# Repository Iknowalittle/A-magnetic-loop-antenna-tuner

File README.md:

This is a simple proto type magnetic loop antenna automatically tune project.
The code can be edit and build with Adunino.

There are somethings that I tried to implemented: 
  1) This stepper motor controller, after some search , finnaly I choose the motor driver chip TMC2209, It has the special function named "sensorless stall detection", which is definitely good 
for Vaccume capacitor because we have no good method to add the physical position limit sensor.
  2) The SWR meter. I use SI5351 act as the signal source and 2 AD8307 chips act as the forard and revese power meter to calculate the SWR.

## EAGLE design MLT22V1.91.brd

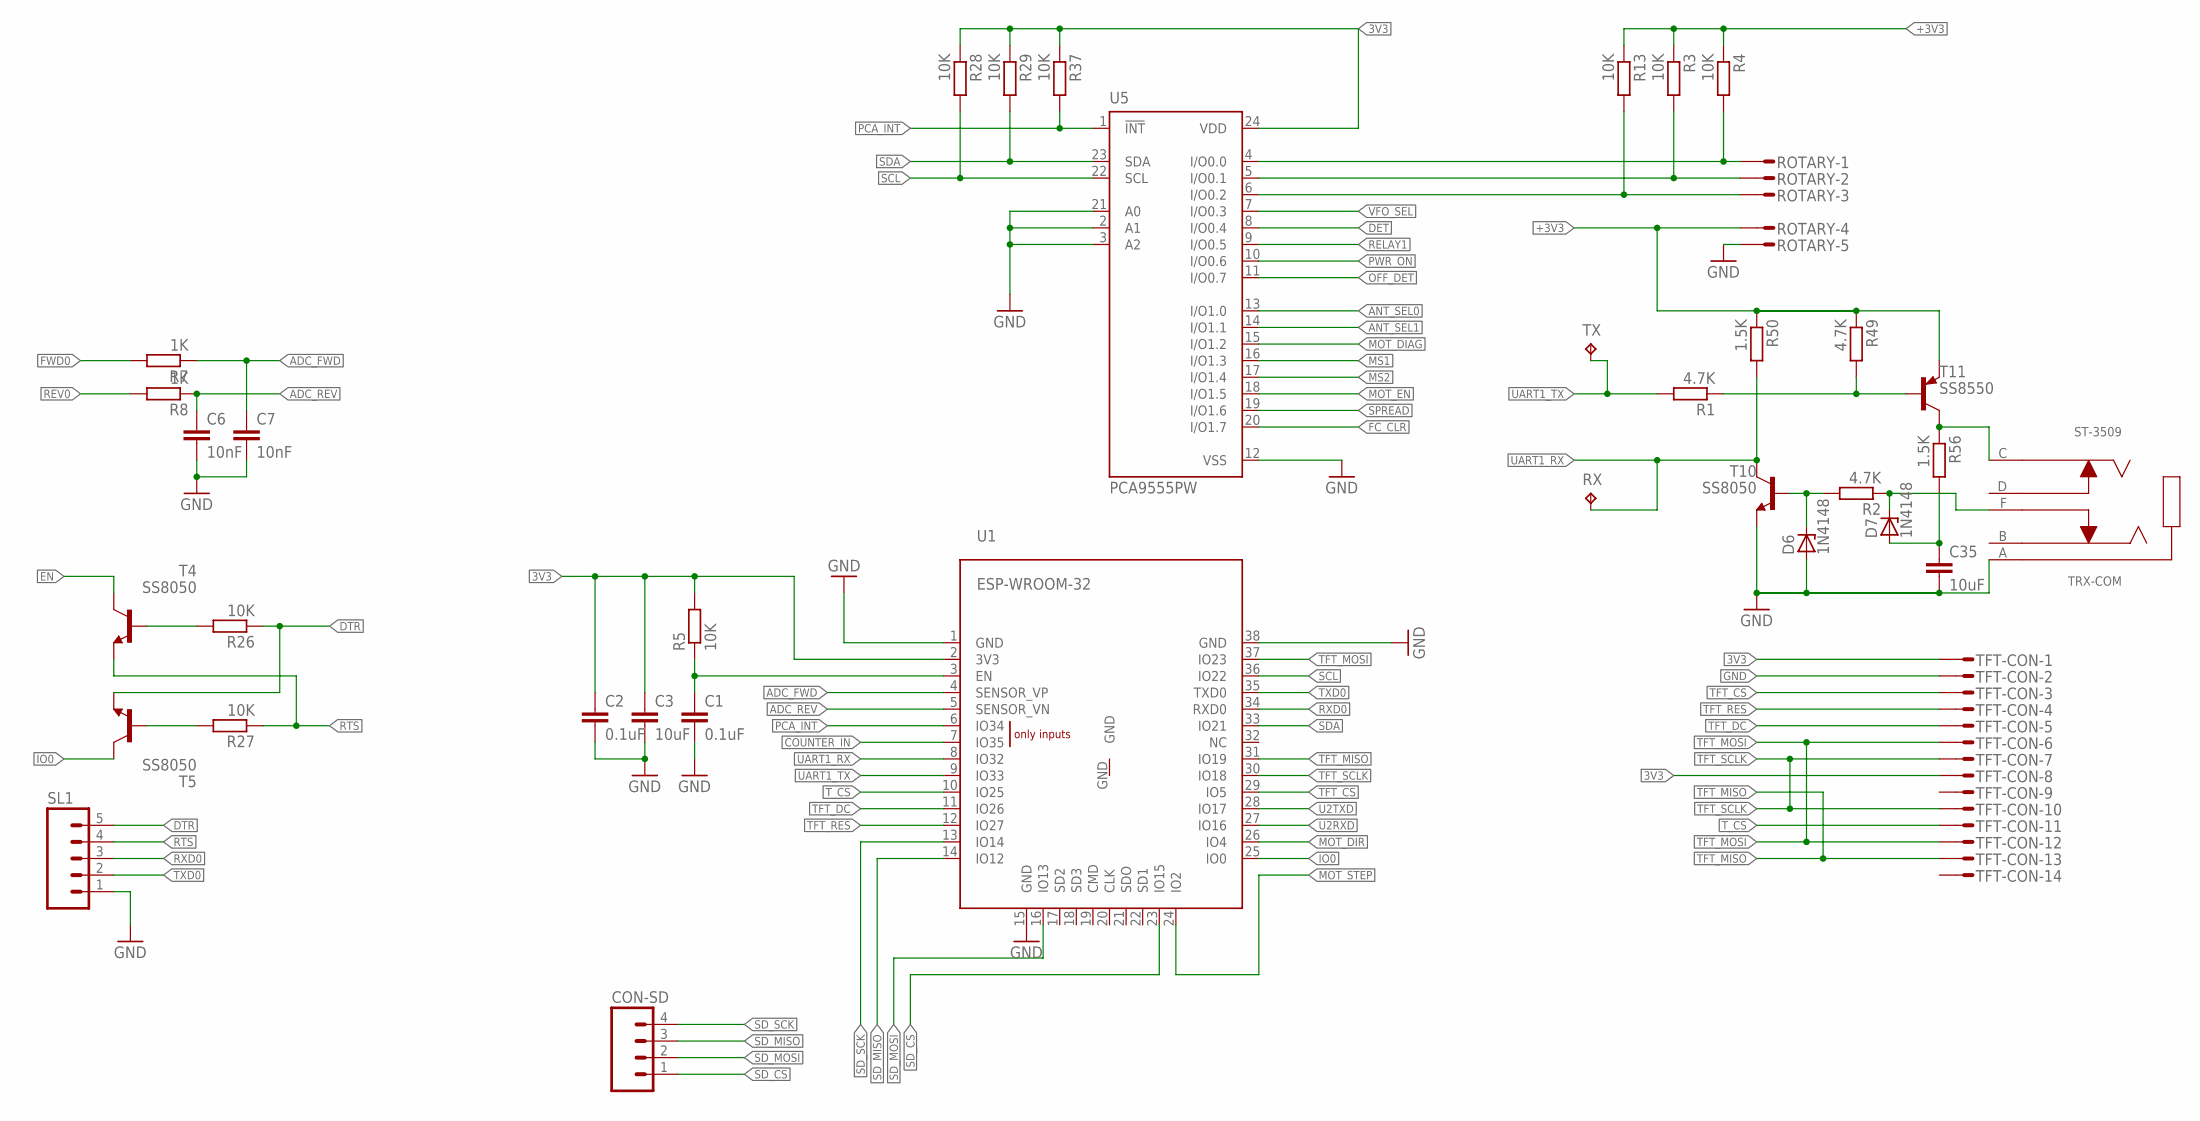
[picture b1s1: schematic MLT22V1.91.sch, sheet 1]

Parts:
C1, C2: 0.1uF; C0603
C3, C35: 10uF; C1206
C6, C7: 10nF; C0603
CON-SD: M04; 04P
D6, D7: 1N4148; SOD80C
R1, R2, R49: 4.7K; R0603
R3, R4, R5, R13, R26, R27, R28, R29, R37: 10K; R0603
R7, R8: 1K; R0603
R50, R56: 1.5K; R0603
ROTARY: S05P
RX: TPTP15R; TP15R
SL1: M05; 05P
T4, T5, T10: SS8050; SOT23-BEC
T11: SS8550; SOT23-BEC
TFT-CON: S14P
TRX-COM: ST-3509
TX: TPTP15R; TP15R
U1: ESP-WROOM-32
U5: PCA9555PW; TSSOP24

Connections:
3V3: C2.1, C3.1, R5.2, R28.1, R29.1, R37.1, TFT-CON.1, TFT-CON.8, U1.2 (3V3), U5.24 (VDD); also elsewhere on the board
+3V3: R3.1, R4.1, R13.1, R49.1, R50.1, ROTARY.4, T11.E; also elsewhere on the board
ADC_FWD: C7.1, R7.1, U1.4 (SENSOR_VP)
ADC_REV: C6.1, R8.1, U1.5 (SENSOR_VN)
ANT_SEL0: U5.13 (I/O1.0); also elsewhere on the board
ANT_SEL1: U5.14 (I/O1.1); also elsewhere on the board
COUNTER_IN: U1.7 (IO35); also elsewhere on the board
DET: U5.8 (I/O0.4); also elsewhere on the board
DTR: R26.1, SL1.5, T5.E
EN: C1.1, R5.1, T4.C, U1.3 (EN)
ENC_SW1: R3.2, ROTARY.2, U5.5 (I/O0.1)
ENC_SW2: R4.2, ROTARY.1, U5.4 (I/O0.0)
FC_CLR: U5.20 (I/O1.7); also elsewhere on the board
FWD0: R7.2; also elsewhere on the board
GND: C1.2, C2.2, C3.2, C6.2, C7.2, C35.2, D6.A, ROTARY.5, SL1.1, T10.E, TFT-CON.2, TRX-COM.A, U1.1 (GND), U1.15 (GND), U1.38 (GND), U5.2 (A1), U5.3 (A2), U5.12 (VSS), U5.21 (A0); also elsewhere on the board
IO0: T5.C, U1.25 (IO0)
MOT_DIAG: U5.15 (I/O1.2); also elsewhere on the board
MOT_DIR: U1.26 (IO4); also elsewhere on the board
MOT_EN: U5.18 (I/O1.5); also elsewhere on the board
MOT_STEP: U1.24 (IO2); also elsewhere on the board
MS1: U5.16 (I/O1.3); also elsewhere on the board
MS2: U5.17 (I/O1.4); also elsewhere on the board
unnamed: R56.1, T11.C, TRX-COM.C
unnamed: R13.2, ROTARY.3, U5.6 (I/O0.2)
unnamed: R1.1, R49.2, T11.B
unnamed: D6.C, R2.2, T10.B
unnamed: R26.2, T4.B
unnamed: R27.2, T5.B
unnamed: C35.1, D7.A, R56.2
unnamed: D7.C, R2.1, TRX-COM.F (E)
OFF_DET: U5.11 (I/O0.7); also elsewhere on the board
PCA_INT: R37.2, U1.6 (IO34), U5.1 (!INT)
PWR_ON: U5.10 (I/O0.6); also elsewhere on the board
RELAY1: U5.9 (I/O0.5); also elsewhere on the board
REV0: R8.2; also elsewhere on the board
RTS: R27.1, SL1.4, T4.E
RXD0: SL1.3, U1.34 (RXD0)
SCL: R28.2, U1.36 (IO22), U5.22 (SCL); also elsewhere on the board
SDA: R29.2, U1.33 (IO21), U5.23 (SDA); also elsewhere on the board
SD_CS: CON-SD.1, U1.23 (IO15)
SD_MISO: CON-SD.3, U1.14 (IO12)
SD_MOSI: CON-SD.2, U1.16 (IO13)
SD_SCK: CON-SD.4, U1.13 (IO14)
SPREAD: U5.19 (I/O1.6); also elsewhere on the board
TFT_CS: TFT-CON.3, U1.29 (IO5)
TFT_DC: TFT-CON.5, U1.11 (IO26)
TFT_MISO: TFT-CON.13, U1.31 (IO19)
TFT_MOSI: TFT-CON.6, TFT-CON.12, U1.37 (IO23)
TFT_RES: TFT-CON.4, U1.12 (IO27)
TFT_SCLK: TFT-CON.7, TFT-CON.10, U1.30 (IO18)
TXD0: SL1.2, U1.35 (TXD0)
T_CS: TFT-CON.11, U1.10 (IO25)
U2RXD: U1.27 (IO16); also elsewhere on the board
U2TXD: U1.28 (IO17); also elsewhere on the board
UART1_RX: R50.2, RX.TP, T10.C, U1.8 (IO32)
UART1_TX: R1.2, TX.TP, U1.9 (IO33)
VFO_SEL: U5.7 (I/O0.3); also elsewhere on the board

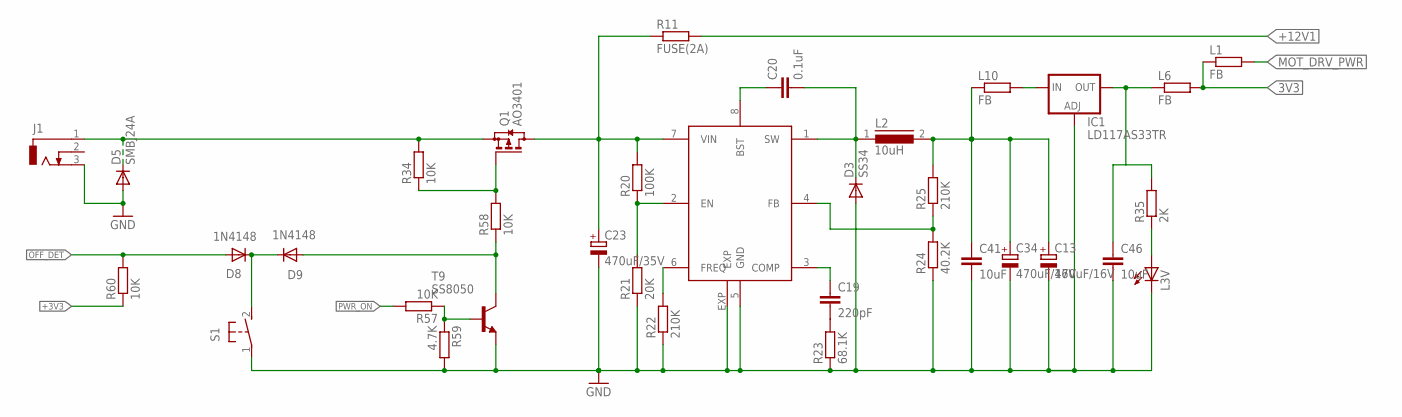
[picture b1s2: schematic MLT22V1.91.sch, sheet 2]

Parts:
C13, C34: 470uF/16V; 153CLV-0605
C19: 220pF; C0603
C20: 0.1uF; C0603
C23: 470uF/35V; 175TMP-0808
C41, C46: 10uF; C1206
D3: SS34; SMB
D5: SMBJ24A; SMB
D8, D9: 1N4148; SOD80C
IC1: LD117AS33TR; SOT223
J1: DCJ0303
L1, L6, L10: FB; R1206
L2: 10uH; DR74
L3V: LEDSML1206; SML1206
Q1: AO3401; SOT23
R11: FUSE(2A); R1206
R20: 100K; R0603
R21: 20K; R0603
R22, R25: 210K; R0603
R23: 68.1K; R0603
R24: 40.2K; R0603
R34, R57, R58, R60: 10K; R0603
R35: 2K; R0603
R59: 4.7K; R0603
S1: 31-XX; B3F-31XX
T9: SS8050; SOT23-BEC
U2: MP1584; SO-8P

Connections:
3V3: L1.1, L6.2; also elsewhere on the board
+3V3: C46.1, IC1.4 (OUT), L6.1, R35.2, R60.1; also elsewhere on the board
+5V: C13.+, C34.+, C41.1, L2.2, L10.1, R25.2; also elsewhere on the board
+12V1: R11.2; also elsewhere on the board
DCDC_BST2: C20.1, U2.8 (BST)
DCDC_COMP2: C19.1, U2.3 (COMP)
DCDC_EN2: R20.1, R21.2, U2.2 (EN)
DCDC_FB2: R24.2, R25.1, U2.4 (FB)
DCDC_SW2: C20.2, D3.C, L2.1, U2.1 (SW)
GND: C13.-, C23.-, C34.-, C41.2, C46.2, D3.A, D5.A, IC1.1 (ADJ), J1.3, L3V.C, R21.1, R22.1, R23.1, R24.1, R59.2, S1.1, T9.E, U2.5 (GND), U2.EXP; also elsewhere on the board
MOT_DRV_PWR: L1.2; also elsewhere on the board
unnamed: L3V.A, R35.1
unnamed: D5.C, J1.1, Q1.2 (S), R34.2
unnamed: C19.2, R23.2
unnamed: IC1.3 (IN), L10.2
unnamed: R22.2, U2.6 (FREQ)
unnamed: Q1.1 (G), R34.1, R58.2
unnamed: R57.1, R59.1, T9.B
unnamed: D8.C, D9.C, S1.2 (S)
unnamed: C23.+, Q1.3 (D), R11.1, R20.2, U2.7 (VIN)
OFF_DET: D8.A, R60.2; also elsewhere on the board
ONOFF: D9.A, R58.1, T9.C
PWR_ON: R57.2; also elsewhere on the board

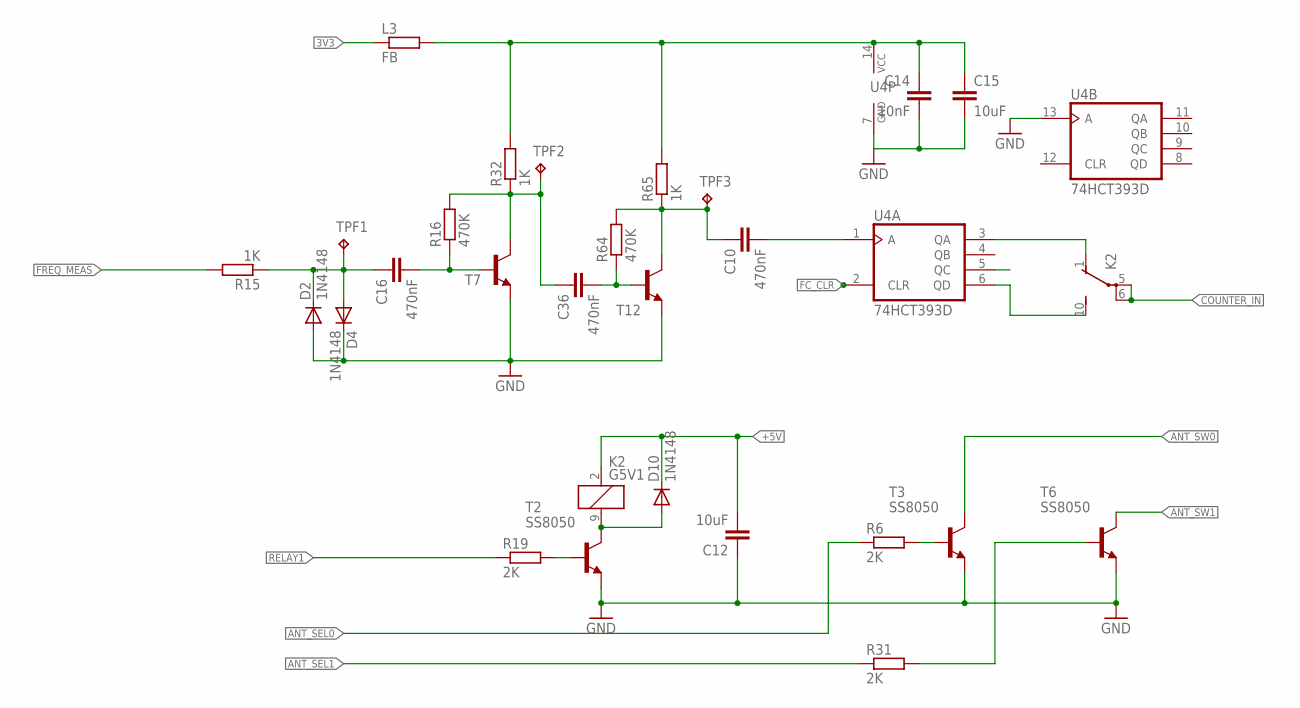
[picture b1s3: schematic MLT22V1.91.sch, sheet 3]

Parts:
C10, C16, C36: 470nF; C0603
C12, C15: 10uF; C1206
C14: 10nF; C0603
D2, D4, D10: 1N4148; SOD80C
K2: G5V1
L3: FB; R1206
R6, R19, R31: 2K; R0603
R15, R32, R65: 1K; R0603
R16, R64: 470K; R0603
T2, T3, T6: SS8050; SOT23-BEC
T7, T12: MMBT3904LT1-NPN-SOT23-BEC; SOT23-BEC
TPF1, TPF2, TPF3: TPTP15R; TP15R
U4: 74HCT393D; SO14

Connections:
3V3: L3.1; also elsewhere on the board
3V3_F: C14.1, C15.1, L3.2, R32.2, R65.2, U4.14 (VCC); also elsewhere on the board
+5V: C12.2, D10.C, K2.2 (1); also elsewhere on the board
ANT_SEL0: R6.1; also elsewhere on the board
ANT_SEL1: R31.1; also elsewhere on the board
ANT_SW0: T3.C; also elsewhere on the board
ANT_SW1: T6.C; also elsewhere on the board
COUNTER_IN: K2.5, K2.6; also elsewhere on the board
FC_CLR: U4.2 (CLR); also elsewhere on the board
FREQIN0: C36.1, R16.2, R32.1, T7.C, TPF2.TP
FREQIN1: C10.1, R64.2, R65.1, T12.C, TPF3.TP
FREQ_BY_16: K2.10 (S), U4.6 (QD)
FREQ_MEAS: R15.2; also elsewhere on the board
GND: C12.1, C14.2, C15.2, D2.A, D4.C, T2.E, T3.E, T6.E, T7.E, T12.E, U4.7 (GND), U4.13 (A); also elsewhere on the board
unnamed: C10.2, U4.1 (A)
unnamed: K2.1 (O), U4.3 (QA)
unnamed: R6.2, T3.B
unnamed: C16.1, D2.C, D4.A, R15.1, TPF1.TP
unnamed: D10.A, K2.9 (2), T2.C
unnamed: R19.2, T2.B
unnamed: R31.2, T6.B
unnamed: C16.2, R16.1, T7.B
unnamed: C36.2, R64.1, T12.B
RELAY1: R19.1; also elsewhere on the board

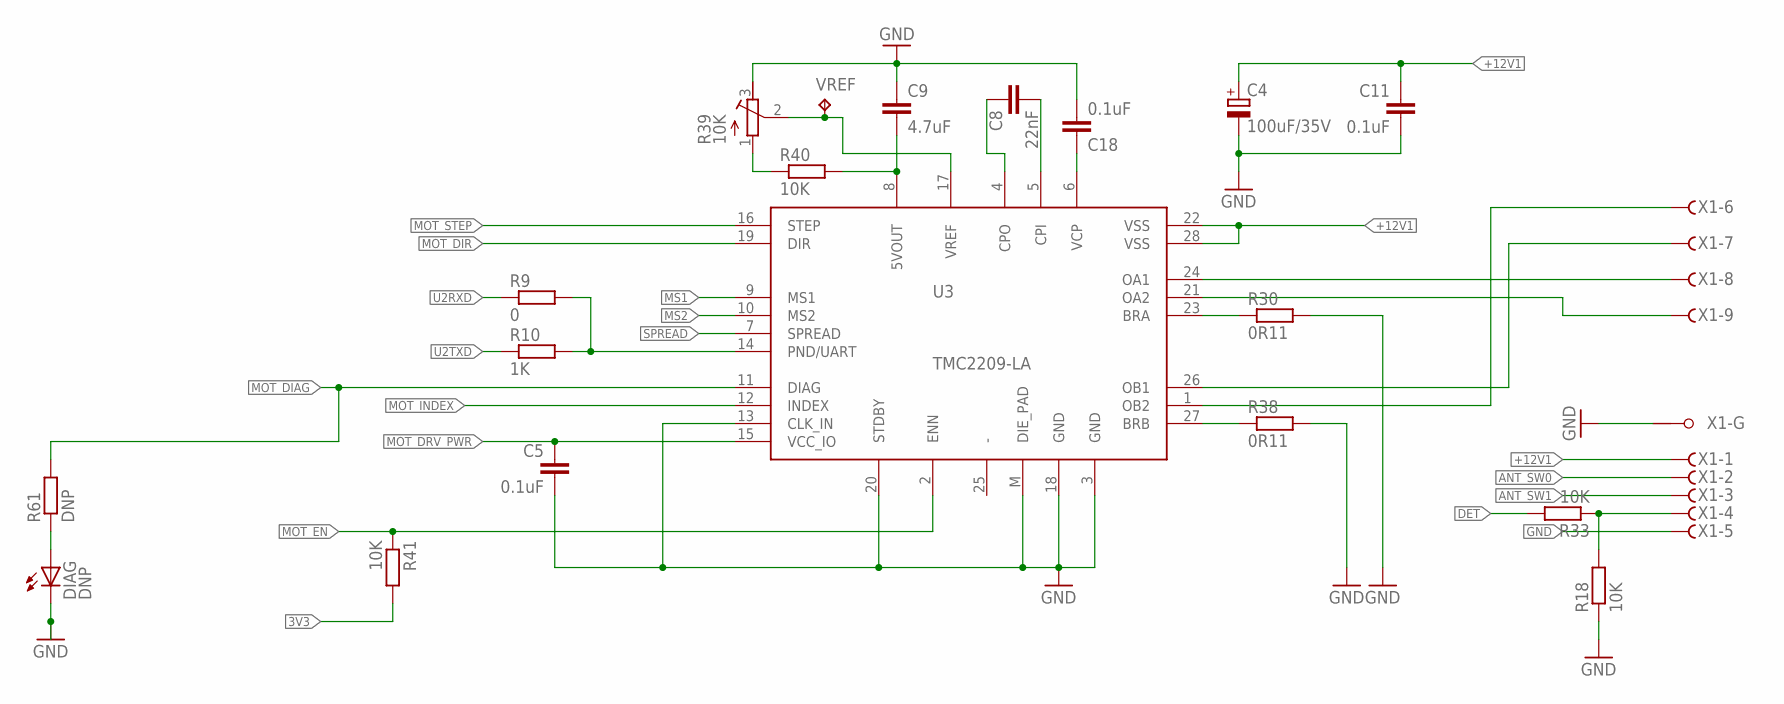
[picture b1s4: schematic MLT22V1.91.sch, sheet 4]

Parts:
C4: 100uF/35V; 150CLZ-1010
C5, C11, C18: 0.1uF; C0603
C8: 22nF; C0603
C9: 4.7uF; C1206
DIAG: DNP; SML1206
R9: 0; R0603
R10: 1K; R0603
R18, R33, R40, R41: 10K; R0603
R30, R38: 0R11; R1206
R39: 10K; RTRIM3103
R61: DNP; R0603
U3: TMC2209-LA; QFN28
VREF: TPB1,27; B1,27
X1: F09HPS; F09HP

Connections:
3V3: R41.2; also elsewhere on the board
5VOUT: C9.2, R40.2, U3.8 (5VOUT)
+12V1: C4.+, C11.1, U3.22 (VSS), U3.28 (VSS), X1.1 (F); also elsewhere on the board
ANT_SW0: X1.2 (F); also elsewhere on the board
ANT_SW1: X1.3 (F); also elsewhere on the board
BRA: R30.1, U3.23 (BRA)
BRB: R38.1, U3.27 (BRB)
CPI: C8.2, U3.5 (CPI)
CPO: C8.1, U3.4 (CPO)
DET: R33.2; also elsewhere on the board
GND: C4.-, C5.2, C9.1, C11.2, C18.2, DIAG.C, R18.1, R30.2, R38.2, R39.3 (E), U3.3 (GND), U3.13 (CLK_IN), U3.18 (GND), U3.20 (STDBY), U3.M (DIE_PAD), X1.5 (F), X1.G1; also elsewhere on the board
MOT_DIAG: R61.2, U3.11 (DIAG); also elsewhere on the board
MOT_DIR: U3.19 (DIR); also elsewhere on the board
MOT_DRV_PWR: C5.1, U3.15 (VCC_IO); also elsewhere on the board
MOT_EN: R41.1, U3.2 (ENN); also elsewhere on the board
MOT_INDEX: U3.12 (INDEX)
MOT_STEP: U3.16 (STEP); also elsewhere on the board
MS1: U3.9 (MS1); also elsewhere on the board
MS2: U3.10 (MS2); also elsewhere on the board
unnamed: DIAG.A, R61.1
unnamed: R39.1 (A), R40.1
unnamed: R18.2, R33.1, X1.4 (F)
OA1: U3.24 (OA1), X1.8 (F)
OA2: U3.21 (OA2), X1.9 (F)
OB1: U3.26 (OB1), X1.7 (F)
OB2: U3.1 (OB2), X1.6 (F)
PD/UART: R9.2, R10.2, U3.14 (PND/UART)
SPREAD: U3.7 (SPREAD); also elsewhere on the board
U2RXD: R9.1; also elsewhere on the board
U2TXD: R10.1; also elsewhere on the board
VCP: C18.1, U3.6 (VCP)
VREF: R39.2 (S), U3.17 (VREF), VREF.TP

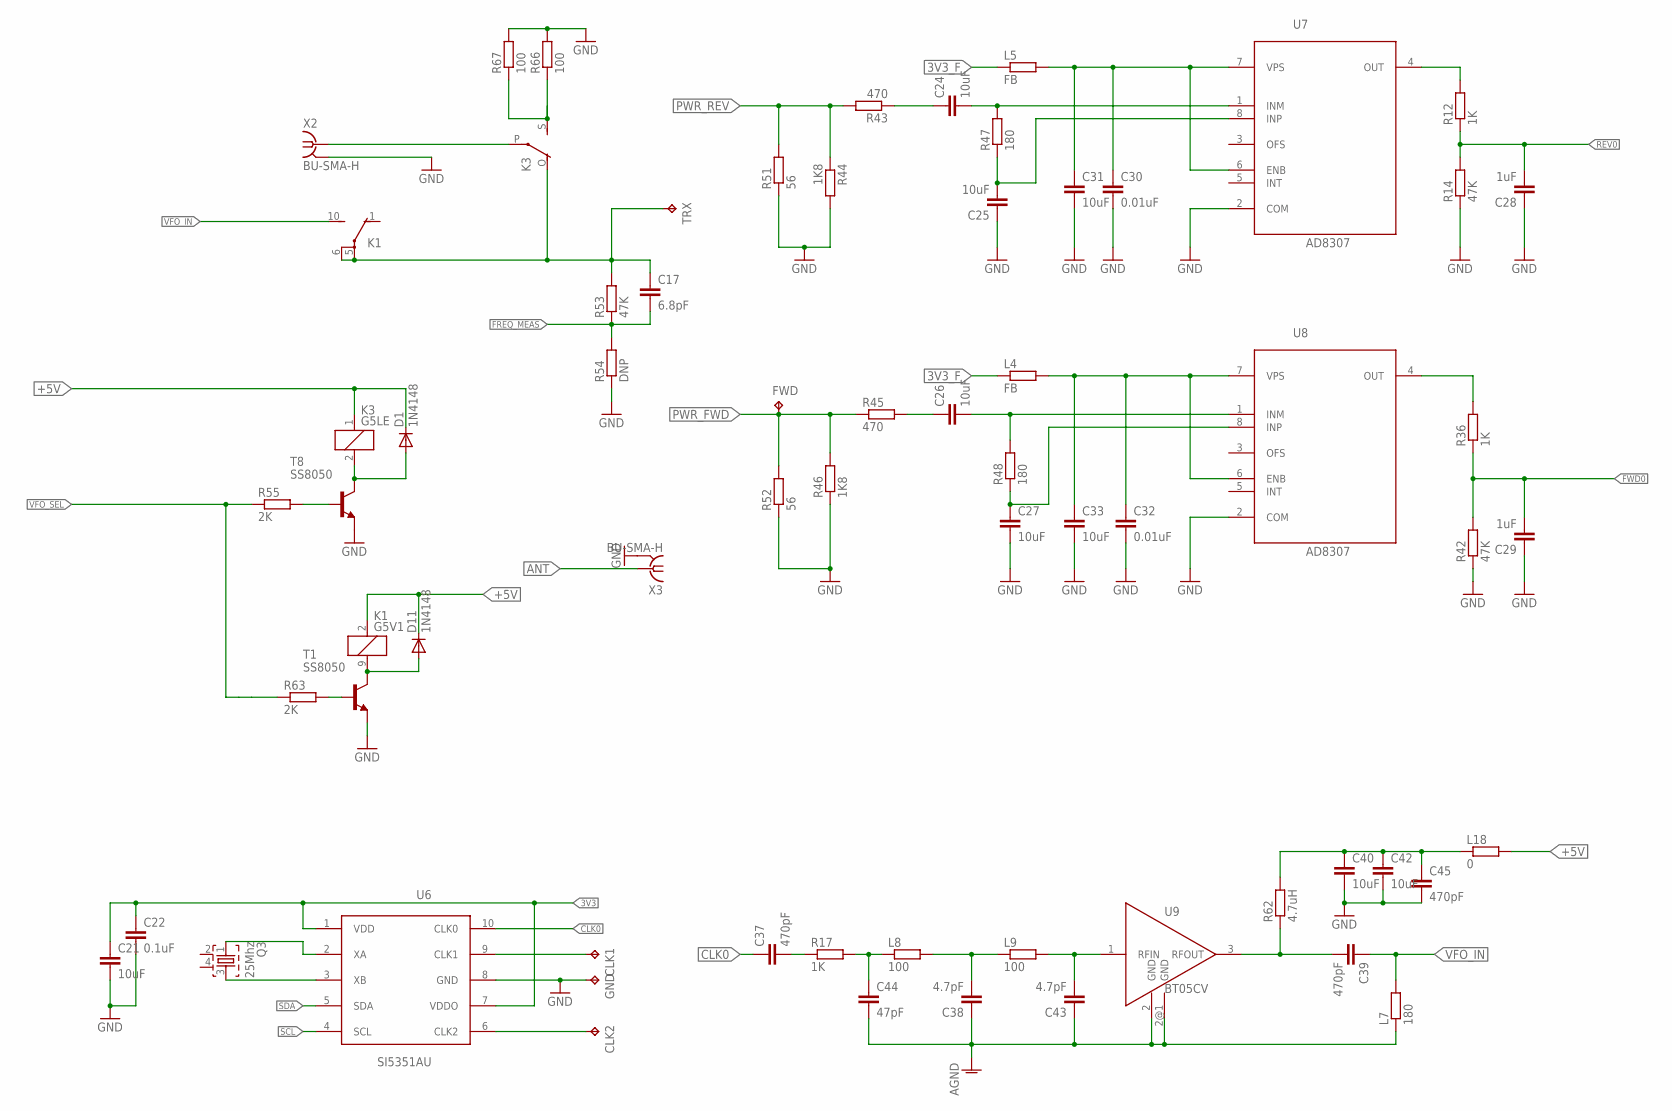
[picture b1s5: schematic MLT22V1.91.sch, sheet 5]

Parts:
C17: 6.8pF; C0603
C21, C24, C25, C26, C27, C31, C33, C40, C42: 10uF; C1206
C22: 0.1uF; C0603
C28, C29: 1uF; C0603
C30, C32: 0.01uF; C0603
C37, C45: 470pF; C0603
C38, C43: 4.7pF; C0603
C39: 470pF; C0805
C44: 47pF; C0603
CLK1, CLK2: TPTP15R; TP15R
D1, D11: 1N4148; SOD80C
FWD: TPPAD1-20; P1-20
GND: TPTP15R; TP15R
K1: G5V1
K3: G5LE
L4, L5: FB; R1206
L7: 180; R0603
L8, L9: 100; R0603
L18: 0; R1206
Q3: 25Mhz; SMD3225
R12, R17, R36: 1K; R0603
R14, R42, R53: 47K; R0603
R43, R45: 470; R1206
R44, R46: 1K8; R1206
R47, R48: 180; R0603
R51, R52: 56; 0922/22
R54: DNP; R0603
R55, R63: 2K; R0603
R62: 4.7uH; R0805
R66, R67: 100; 0922/22
T1, T8: SS8050; SOT23-BEC
TRX: TPPAD1-20; P1-20
U6: SI5351AU; MSOP10
U7, U8: AD8307; SO08
U9: BT05CV; SOT89
X2, X3: BU-SMA-H

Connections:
3V3: C21.1, C22.1, U6.1 (VDD), U6.7 (VDDO); also elsewhere on the board
3V3_F: L4.1, L5.1; also elsewhere on the board
+5V: D1.C, D11.C, K1.2 (1), K3.1, L18.2; also elsewhere on the board
ANT: X3.1
CLK0: C37.1, U6.10 (CLK0)
CLK1: CLK1.TP, U6.9 (CLK1)
CLK2: CLK2.TP, U6.6 (CLK2)
FREQ_MEAS: C17.2, R53.1, R54.2; also elsewhere on the board
FWD0: C29.2, R36.1, R42.2; also elsewhere on the board
GND: C21.2, C22.2, C25.1, C27.2, C28.1, C29.1, C30.2, C31.2, C32.2, C33.2, C38.1, C40.2, C42.2, C43.1, C44.2, C45.2, GND.TP, L7.1, R14.1, R42.1, R44.2, R46.1, R51.1, R52.1, R54.1, R66.2, R67.2, T1.E, T8.E, U6.8 (GND), U7.2 (COM), U8.2 (COM), U9.2 (GND), U9.2@1 (GND), X2.2, X2.3 (2), X2.4 (2), X2.5 (2), X3.2, X3.3 (2), X3.4 (2), X3.5 (2); also elsewhere on the board
unnamed: C24.2, R47.2, U7.1 (INM)
unnamed: C25.2, R47.1, U7.8 (INP)
unnamed: C24.1, R43.1
unnamed: C30.1, C31.1, L5.2, U7.6 (ENB), U7.7 (VPS)
unnamed: R12.2, U7.4 (OUT)
unnamed: R55.2, T8.B
unnamed: C32.1, C33.1, L4.2, U8.6 (ENB), U8.7 (VPS)
unnamed: D1.A, K3.2, T8.C
unnamed: K3.S, R66.1, R67.1
unnamed: C27.1, R48.1, U8.8 (INP)
unnamed: C26.2, R48.2, U8.1 (INM)
unnamed: C26.1, R45.2
unnamed: R36.2, U8.4 (OUT)
unnamed: Q3.1, U6.2 (XA)
unnamed: Q3.3, U6.3 (XB)
unnamed: C38.2, L8.2, L9.1
unnamed: C43.2, L9.2, U9.1 (RFIN)
unnamed: C39.2, R62.1, U9.3 (RFOUT)
unnamed: D11.A, K1.9 (2), T1.C
unnamed: R63.2, T1.B
unnamed: C37.2, R17.1
unnamed: C44.1, L8.1, R17.2
PA3V: C40.1, C42.1, C45.1, L18.1, R62.2
PWR_FWD: FWD.TP, R45.1, R46.2, R52.2
PWR_REV: R43.2, R44.1, R51.2
REV0: C28.2, R12.1, R14.2; also elsewhere on the board
SCL: U6.4 (SCL); also elsewhere on the board
SDA: U6.5 (SDA); also elsewhere on the board
TRX: C17.1, K1.5, K1.6, K3.O, R53.2, TRX.TP
TRX_IN: K3.P, X2.1
VFO_IN: C39.1, K1.10 (S), L7.2
VFO_SEL: R55.1, R63.1; also elsewhere on the board

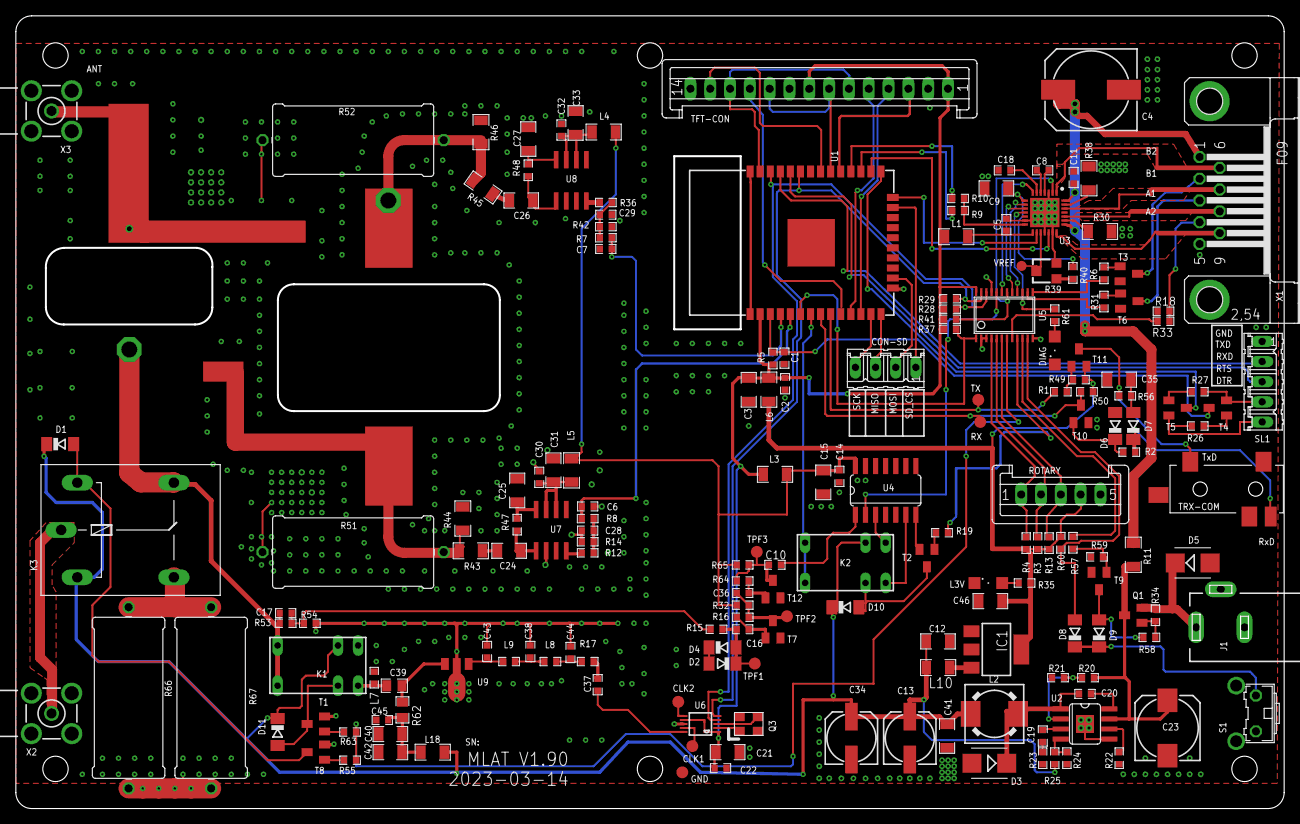
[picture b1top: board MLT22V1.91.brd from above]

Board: 2 copper layers, 159.7 x 99.7 mm, 185 parts (0 on the bottom side), 137 nets.

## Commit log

2024-09-07 GUI slice file
    UI file, open with GUISlice
2024-10-16 eagle schematic and board
